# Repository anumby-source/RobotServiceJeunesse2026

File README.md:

# Projet RobotServiceJeunesse2026

# Réflexions préparatoires pour le projet Jeunesse 2026

Le projet Jeunesse aura lieu dans une 1/2 journée dans les vacances pâques 2026 à choisir. 
Faire attention pour la durée: discuter avec les organisateurs pour obtenir réellement les 3 heures de le demie journée.

Principe: On garde le proto de l'année dernière mais avec quelques corrections (et/ou améliorations)

- Meilleurs moteurs plus rapides (choix des roues)
- Mener des tests pour fiabiliser l'utilisation de Esp now
- choisir le CPU de base: Esp32 s2 s3? C3?
  - impact: nombre de DIOs
  - tester la nécessité d'une vraie antenne
  - Nouveau proto (encombrement)
- Pilotage
- nouveau design pour le circuit
- utilisation d'un Microphone?
- IA ? Reconnaissance de symboles plutôt que caractères

- Refaire la télécommande. tests de Fiabilité
- Pb de multicanal sur la communication: tests
- utilisation de Powerbank 5V
- Reconnaissance par le k210 ?

## Organisation:
- distribuer les rôles pour les éléments à re-tester (moteurs, communication, reconnaissance, circuit, achats)
- mettre en place un Github 2026

# Benchmark ESP-now sur ESP32 S3

En menant mon benchmark esp-now j'ai compris qu'il faut flasher micropython >= 1.26 (au moins) car c'est à partir de cette version de micropython que Esp-now, est inclus dans micropython.
Par défaut 1.19 était flashé sur le ESP32-S3.
Pas grave mais il suffisait de le savoir.

# Convention d'identification pour ESP32-S3

ESP32-S3-N8R2

Chez Espressif, cette nomenclature signifie :

N8 → 8 MB de Flash
R2 → 2 MB de PSRAM

# IDF and HEAP in ESP32

list_of_tuples = esp32.idf_heap_info(esp32.HEAP_DATA )

each tuple in list_of_tuples is:
- total bytes
- the free bytes
- the largest free block

# Discussion mardi 13 janvier sur projet Jeunesse

- Alimentation Powerbank ok 18650 (vérifications pour la stabilité cependant)
- Gilles a préparé une nouvelle implémentation de l'ensemble, avec S2 (avec l'antenne améliorée)
  + une résistance de charge 
  + Logiciel sans changement 
  + Une néo pixel qu'il faudra intégrer au soft

- Détection de symboles avec k210 plutôt que nom des villes 

- Possibilité de fournir la version aux jeunes avec un capteur de distance à la place du k210

- on garde des options avec esp32 s3 cam ? mais l'option de base préférée est celle qui garanti le moindre changements

- Pb de la télécommande 
    + Batterie changer ?
    + version Ttgo esp32 avec afficheur + chargeur 
    + Ajouter vitesse lente.

# Programme de base pour le jeu Robot

Le programme base.py implémente la connexion entre le cpu du Robot et l'écran de contrôle

Le principe de base consiste à recevoir les messages (canal espnow) qui reflètent les panneaux routiers détectés par la caméra du K210.

l'IHM de base.py montre tous les messages reçus et décode ces messages en allumant les boutons des panneaux.

Etat d'avancement du programme de base:

- le programme base tourne sur un esp32
- c'est un serveur Web utilisant les SSE
- il est connecté espnow avec les CPUs de deux robots.
  => il faudra assurer que la mac adresse du ESP32 de base est déclarée
     dans le fichier mac_addr 
- actuellement la base est sensible aux valeurs d'ID de panneaux transférés via espnow mais il est 
  aussi sensible de façon équivalente aux boutons équivalents de l'IHM de la base
- il reste à ajouter la propagation des valeur de la vitesse (0, v1, v2) qui est nécessaire pour
  faire fonctionner le protocole du jeu.
- actuellement du protocole de jeu est simplifié
     - Le bouton global "START" lance les deux jeux pour les deux robots
     - on attend la reconnaissance du panneau "start"
     - ensuite tous les panneaux sont reconnus mais n'influencent pas le jeu
     - en suite la reconnaissance de "stop" arrête le jeu
     - l'IHM met à jour le temps courant de parours
     - on ne comptabilise pas le pénalités pour l'instant
     - le bouton global "RESET" réinitialise les deux jeux

Les messages espnow fournissent automatiquement l'adresse MAC du robot appelant.
Le logiciel va attribuer le premier robot ayant parlé au côté "A" et le deuxième au côté "B"

# Logique des événements dans le programme base.

On gère plusieurs sources d'événements:
- il y a ce qui vient de espnow: ce sont des événements produits par les robots. Ces messages contienent:
   - Les ID des panneaux reconnus par le K210
   - l'état du moteurs (=> vitesse=0, v1, v2)
   - avec le format: "PID=ID,vitesse"
- il y a ce qui vient de l'IHM (à travers des appels (fetch("key=data"))

Les événements espnow sont mis en queue dans la queue "queue_espnow", qui est elle-même exploitée (dépilée) par la fonction
"espnow_dispatcher", qui transforme les evts "espnow" en evts SSE. Ces événements ont le format "PID=data"

Ces événements produisent tous des messages SSE, qui sont mis en queue d'attente dans la queue "queue_sse".
La queue "queue_sse" est dépilée par la fonction du serveur "Server.sse_broadcaster()".
Les événements SSE sont traités dans le script JS dans le fonction du gestionnaire "EventSource" 
  - déclarée par "var E = new EventSource('/events');"
  - qui est appelé par "E.onmessage = function(e) {...}"
  - un événement SSE transféré de espnow va émuler un click par l'appel interne de la fonction "onclick" attachée aux boutons

Cette fonction produit en particulier des actions directes sur des éléments de l'IHM du style "document.getElementById(<element_id>).style.background='red';"

L'IHM est structurée avec:
- des éléments de contrôle généraux
    - pour démarrer le jeu ou réinitialiser les données du jeu
- une table à deux colonnes: pour chacun des deux joueurs:
    - des boutons pour émuler les panneaux si on fonctionne sans connexion avec les robots ou pour refléter les panneaux effectivement reconnus
    - un panneau des valeurs du jeu, mises à jours en temps réel.

Routes:

- START: démarrage général du jeu
- RESET: réinitialsation générale du jeu
- APID: message espnow du robot A
- BPID: message espnow du robot B
- ABTN: message IHM du joueur A
- BBTN: message IHM du joueur B
- AVALUES: valeurs jeu du joueur A
- BVALUES: valeurs jeu du joueur B

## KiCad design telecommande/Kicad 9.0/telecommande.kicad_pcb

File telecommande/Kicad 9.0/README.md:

# Fichiers Kicad du pcb telecommande

<p align="center"> 
   
<p/>

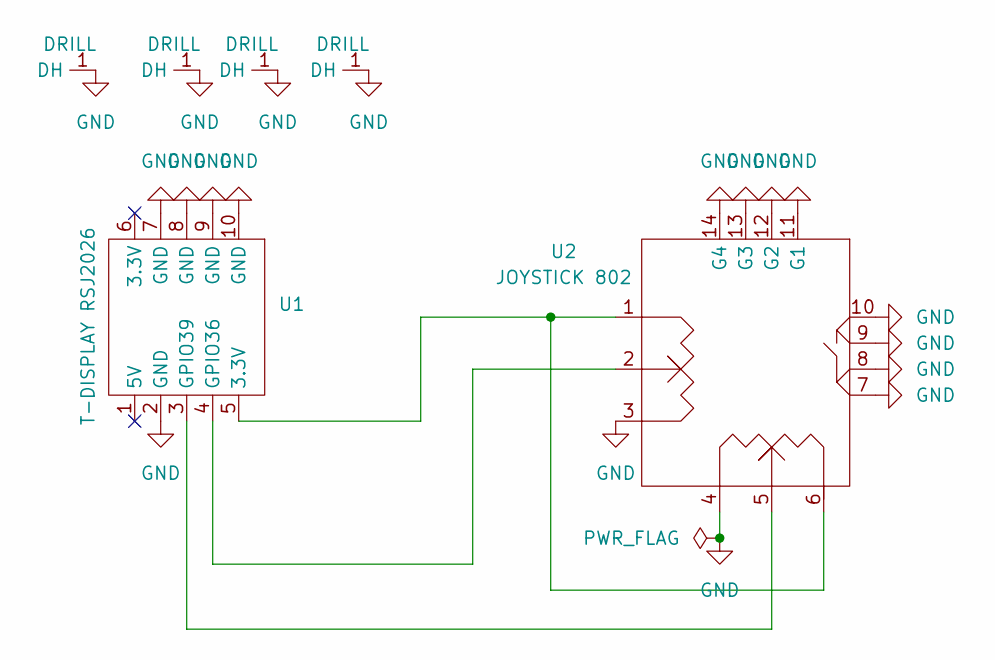
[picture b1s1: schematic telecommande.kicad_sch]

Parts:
DH1, DH2, DH3, DH4: DRILL; DRILL_HOLE
U1: T-DISPLAY RSJ2026; TTGO T-DISPLAY RSJ2026
U2: JOYSTICK 802; JOYSTICK_MODEL_802

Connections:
GND: DH1.1 (DH), DH2.1 (DH), DH3.1 (DH), DH4.1 (DH), U1.2 (GND), U1.7 (GND), U1.8 (GND), U1.9 (GND), U1.10 (GND), U2.3, U2.4, U2.7, U2.8, U2.9, U2.10, U2.11 (G1), U2.12 (G2), U2.13 (G3), U2.14 (G4)
unnamed: U1.5 (3.3V), U2.1, U2.6
unnamed: U1.4 (GPIO36), U2.2
unnamed: U1.3 (GPIO39), U2.5

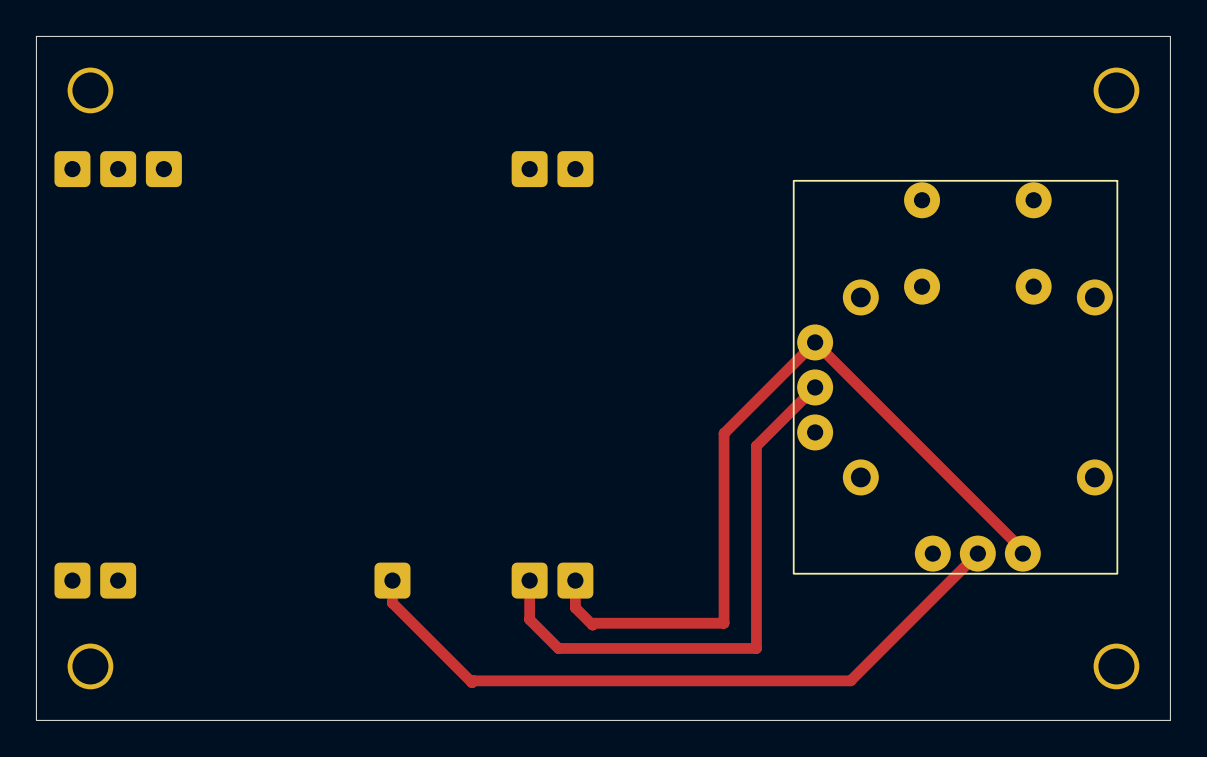
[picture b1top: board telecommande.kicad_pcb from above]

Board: 2 copper layers, 63.0 x 38.0 mm, 6 parts (0 on the bottom side), 4 nets.

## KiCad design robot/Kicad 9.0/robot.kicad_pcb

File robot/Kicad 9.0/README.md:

# Fichiers Kicad du pcb robot

<p align="center"> 
   
<p/>

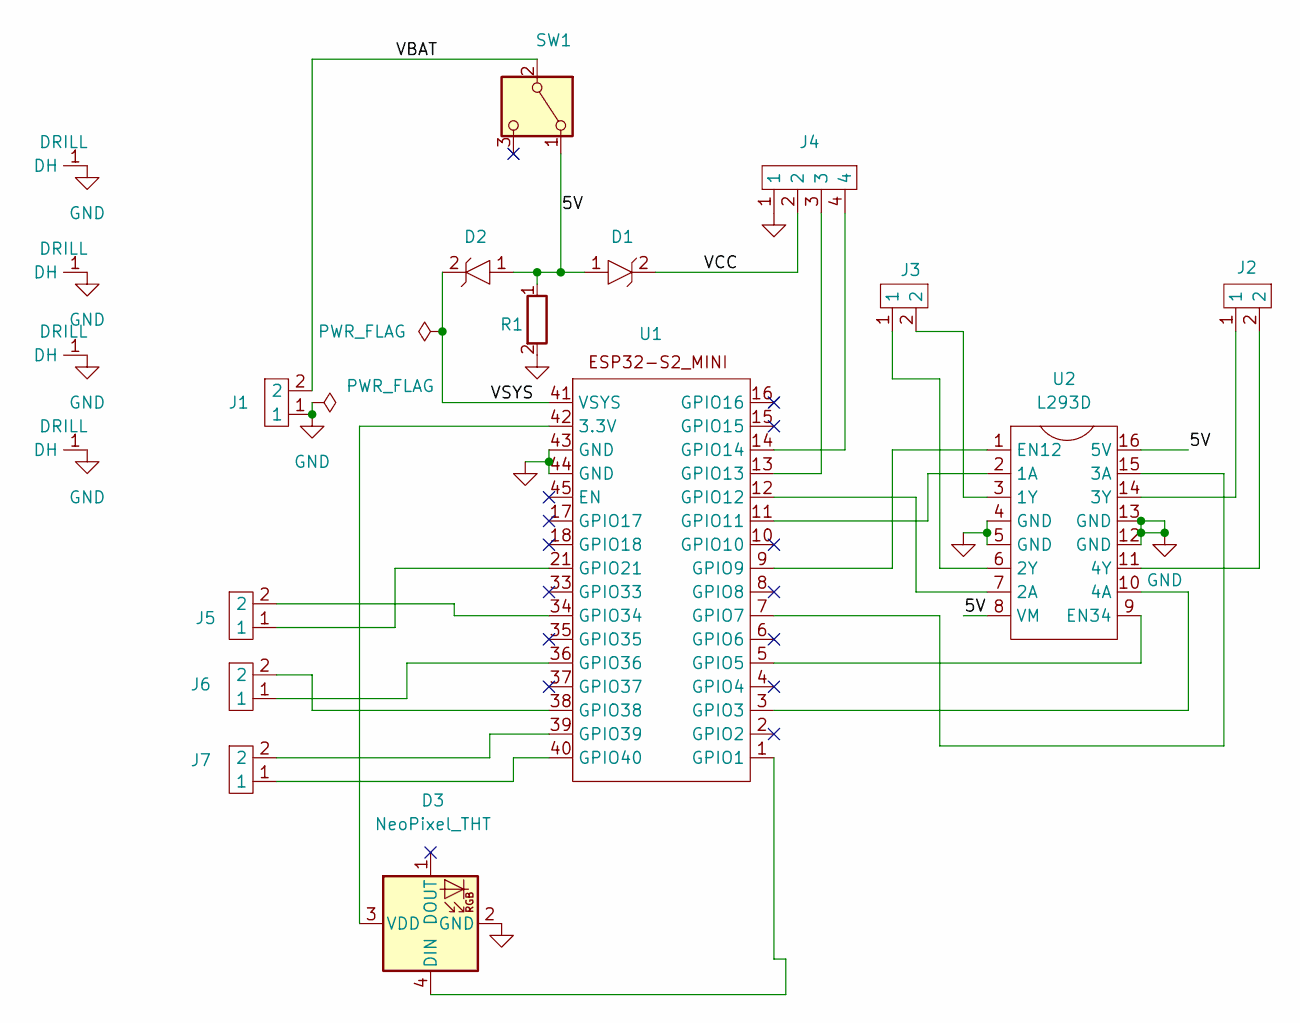
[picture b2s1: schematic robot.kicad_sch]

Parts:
D1, D2: 1N5818
D3: NeoPixel_THT; NeoPixel
DH1, DH2, DH3, DH4: DRILL; DRILL_HOLE
J1, J2, J3, J5, J6, J7: XH2.54_2P_socket; XH2.54_2P_soc
J4: XH2.54_4P_socket; XH2.54_4P_soc
R1: R_0.25W
SW1: SW_MINI_x1; SW_MINI_X1
U1: ESP32-S2_MINI
U2: L293D

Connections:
/5V: D1.1, D2.1, R1.1, SW1.1 (A), U2.8 (VM), U2.16 (5V)
/VBAT: J1.2, SW1.2 (B)
/VCC: D1.2, J4.2
/VSYS: D2.2, U1.41 (VSYS)
GND: D3.2 (GND), DH1.1 (DH), DH2.1 (DH), DH3.1 (DH), DH4.1 (DH), J1.1, J4.1, R1.2, U1.43 (GND), U1.44 (GND), U2.4 (GND), U2.5 (GND), U2.12 (GND), U2.13 (GND)
unnamed: D3.4 (DIN), U1.1 (GPIO1)
unnamed: D3.3 (VDD), U1.42 (3.3V)
unnamed: U1.3 (GPIO3), U2.10 (4A)
unnamed: U1.5 (GPIO5), U2.9 (EN34)
unnamed: U1.7 (GPIO7), U2.15 (3A)
unnamed: U1.9 (GPIO9), U2.1 (EN12)
unnamed: U1.11 (GPIO11), U2.2 (1A)
unnamed: U1.12 (GPIO12), U2.7 (2A)
unnamed: J4.3, U1.13 (GPIO13)
unnamed: J4.4, U1.14 (GPIO14)
unnamed: J5.1, U1.21 (GPIO21)
unnamed: J5.2, U1.34 (GPIO34)
unnamed: J6.1, U1.36 (GPIO36)
unnamed: J6.2, U1.38 (GPIO38)
unnamed: J7.2, U1.39 (GPIO39)
unnamed: J7.1, U1.40 (GPIO40)
unnamed: J3.2, U2.3 (1Y)
unnamed: J3.1, U2.6 (2Y)
unnamed: J2.1, U2.14 (3Y)
unnamed: J2.2, U2.11 (4Y)

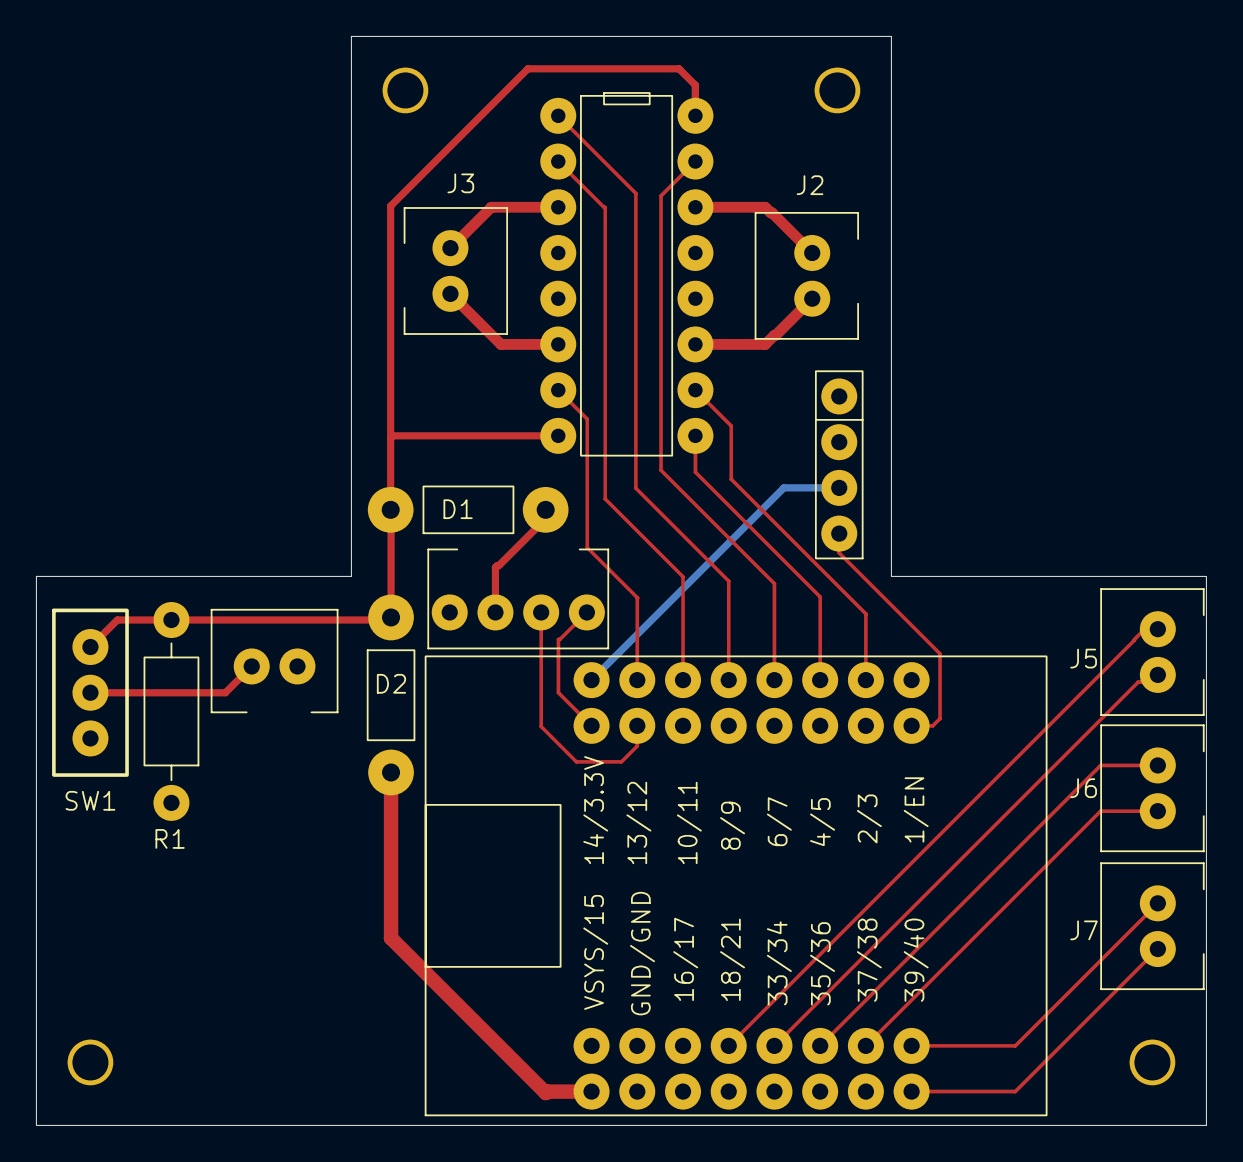
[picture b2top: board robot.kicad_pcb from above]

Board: 2 copper layers, 65.0 x 60.5 mm, 18 parts (0 on the bottom side), 25 nets.

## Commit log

2025-12-22 Add README.md
2025-12-22 Add .gitignore
2025-12-22 README.md
2025-12-28 Tests esp-now entre 2 ESP32S3
2025-12-29 Tests esp-now entre 2 ESP32S3 arrêt CTL-C controllé
2026-01-17 Tests communication série entre 2 ESP32 et K210
2026-01-17 Commandes pour la capture d'images associées à N identifiants
2026-01-17 images de panneaux
2026-01-19 Version sender + receiver sans apprentissage
2026-01-24 Ajoute de la documentation Sipeed
2026-01-24 Ajoute un pgm de test de la caméra
2026-01-24 Apprentissage: initialisation des classes
2026-01-25 Apprentissage avec l'outil MaixHub
2026-01-30 Apprentissage avec l'outil MaixHub panneaux: 1 2 3 4 5 6 8 13 17
2026-01-30 Apprentissage avec l'outil MaixHub panneaux: labels = ['04', '06', '01', '02', '03', '05', '08', '13', '17']
2026-03-03 Add initial README for ROBOT 2026
2026-03-03 Update README format for ROBOT 2026
2026-03-03 Add README.md for Kicad PCB files
2026-03-03 Add README file for Telecommande 2026
2026-03-03 Enhance README with image and formatting
    Add image and center alignment to README
2026-03-03 Change PCB image to electrical schematic image
    Updated image source in README for robot PCB.
2026-03-03 Add image to README for telecommande PCB
2026-03-03 Update README with 2026 version features
    Added details about the new features in the 2026 version.
2026-03-03 Revise hardware details in README.md
    Updated the README to reflect changes in hardware specifications.
2026-03-16 Add README.md for robot 3D printing files
2026-03-16 Add README.md for 3D remote control files
2026-03-16 Reprise des développements depuis le dossier ESP32S3Cam
2026-03-17 Add boot.py description to README.md
2026-03-18 Panneaux.pptx version plus petite
2026-03-19 Intégration
2026-03-19 Protocoles
2026-03-24 Mise en place de la base avec la technologie des événements SSE
2026-03-24 Mise en place de la base avec la technologie des événements SSE les messages espnow générent des evt SSE pour être exploités dans le client
2026-03-25 Mise en place du jeu.
2026-03-26 Mise en place de la gestion à deux joueurs et donc avec deux robots.
2026-03-26 Mise en place de la gestion à deux joueurs et donc avec deux robots. Les clicks et le messages espnow sont équivalents
2026-03-31 finalisation des fichiers à installer
2026-03-31 finalisation des fichiers à installer prépare un dossier Python d'installation en préservant les anciens fichiers en développement
2026-05-06 Protocole de broadcast pour que la base détecte les mac adresses des robots, et pour que chaque robot reçoivent la mac adresse de la base.
2026-05-11 Ajout du mécanisme de broadcast pour rendre l'initialisation des robots, base, télécommandes sans mémoriser la mac-add de la base
2026-05-12 Par défaut, on est en mode simulation de robots simulés. Dès qu'un robot se connecte, on débranche le mode simulation. De même, le bouton reset simule 2 robots si la simulation est ON. Le bouton rese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
2026-05-19 debugging connection des robots, association des robots avec l'IHM dans base
